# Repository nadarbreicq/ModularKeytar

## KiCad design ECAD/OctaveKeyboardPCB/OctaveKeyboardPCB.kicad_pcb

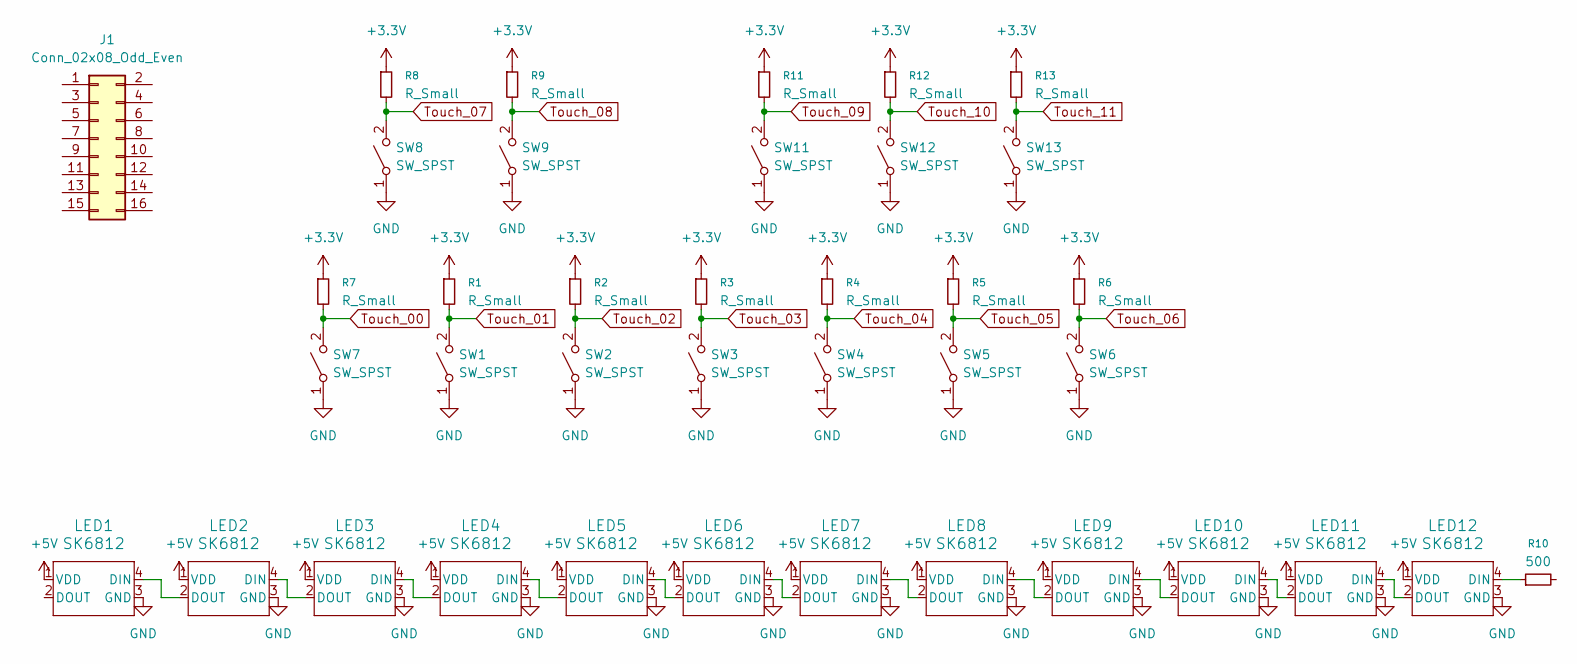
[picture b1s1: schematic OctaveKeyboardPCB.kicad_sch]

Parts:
J1: Conn_02x08_Odd_Even; IDC-Header_2x08_P2.54mm_Vertical
LED1, LED2, LED3, LED4, LED5, LED6, LED7, LED8, LED9, LED10, LED11, LED12: SK6812; SK6812-E-4960_ADA
R1, R2, R3, R4, R5, R6, R7, R8, R9, R11, R12, R13: R_Small; R_1206_3216Metric_Pad1.30x1.75mm_HandSolder
R10: 500; R_1206_3216Metric_Pad1.30x1.75mm_HandSolder
SW1, SW2, SW3, SW4, SW5, SW6, SW7, SW8, SW9, SW11, SW12, SW13: SW_SPST; SW_Cherry_MX_PCB_1.00u

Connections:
+3.3V: R1.1, R2.1, R3.1, R4.1, R5.1, R6.1, R7.1, R8.1, R9.1, R11.1, R12.1, R13.1
+5V: LED1.1 (VDD), LED2.1 (VDD), LED3.1 (VDD), LED4.1 (VDD), LED5.1 (VDD), LED6.1 (VDD), LED7.1 (VDD), LED8.1 (VDD), LED9.1 (VDD), LED10.1 (VDD), LED11.1 (VDD), LED12.1 (VDD)
GND: LED1.3 (GND), LED2.3 (GND), LED3.3 (GND), LED4.3 (GND), LED5.3 (GND), LED6.3 (GND), LED7.3 (GND), LED8.3 (GND), LED9.3 (GND), LED10.3 (GND), LED11.3 (GND), LED12.3 (GND), SW1.1 (A), SW2.1 (A), SW3.1 (A), SW4.1 (A), SW5.1 (A), SW6.1 (A), SW7.1 (A), SW8.1 (A), SW9.1 (A), SW11.1 (A), SW12.1 (A), SW13.1 (A)
unnamed: LED1.4 (DIN), LED2.2 (DOUT)
unnamed: LED2.4 (DIN), LED3.2 (DOUT)
unnamed: LED3.4 (DIN), LED4.2 (DOUT)
unnamed: LED4.4 (DIN), LED5.2 (DOUT)
unnamed: LED5.4 (DIN), LED6.2 (DOUT)
unnamed: LED6.4 (DIN), LED7.2 (DOUT)
unnamed: LED7.4 (DIN), LED8.2 (DOUT)
unnamed: LED8.4 (DIN), LED9.2 (DOUT)
unnamed: LED10.4 (DIN), LED11.2 (DOUT)
unnamed: LED9.4 (DIN), LED10.2 (DOUT)
unnamed: LED11.4 (DIN), LED12.2 (DOUT)
unnamed: LED12.4 (DIN), R10.1
Touch_00: R7.2, SW7.2 (B)
Touch_01: R1.2, SW1.2 (B)
Touch_02: R2.2, SW2.2 (B)
Touch_03: R3.2, SW3.2 (B)
Touch_04: R4.2, SW4.2 (B)
Touch_05: R5.2, SW5.2 (B)
Touch_06: R6.2, SW6.2 (B)
Touch_07: R8.2, SW8.2 (B)
Touch_08: R9.2, SW9.2 (B)
Touch_09: R11.2, SW11.2 (B)
Touch_10: R12.2, SW12.2 (B)
Touch_11: R13.2, SW13.2 (B)

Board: 2 copper layers, 38 parts (24 on the bottom side), 27 nets, no tracks yet.

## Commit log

2025-04-04 WIP - Live 223
